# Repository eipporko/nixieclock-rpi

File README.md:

6 digit Nixie Clock
===================

## Motivation

* [Alex's Nixie Clock](https://www.raspberrypi.org/blog/alexs-nixie-clock/)

## Project structure

 * `hardware/eagle` - PCB design and schematics
 * `hardware/docs`  - various PDF datasheets for components used
 * `software`       - clock program

## BOM Summary
Main components

 * IN-8-2 Nixie tubes
 * MH74141 Nixie driver
 * 74HCT259 8-bit addressable latch
 * SN74LS77 4-bit D latch
 * ULN2803A Eight Darligton array
 * Raspberry Pi Zero, 1, 2 or 3 (Models B, B+)

The BCD decoder IC and Nixie tubes is hard to obtain, so far they're only
available on ebay and most of them are NOS(new old stock)

Check the schematics for the rest of the passives

## Theory of operation

### Architecture
Every digit of the display is composed by a Nixie tube (IN-8-2) driven by a
decimal decoder designed for directly drive this kind of gas-filled cold-cathode
indicators (MH74141) which input is supplied by a 4-bit D Latch (SN74LS77).

Each latch is multiplexed, with one 3-line to 8-line demux with latch (74HCT259),
in order to share the 4 bit bus with all the drivers.

In this way it's only needed 8 bits to control the clock's display.

```
** RPI GPIO HEADER SCHEMATIC **
                            .___.
                   +3V3---1-|O O|--2--+5V
           (SDA)  GPIO2---3-|O O|--4--+5V
          (SCL1)  GPIO3---5-|O O|--6--_
     (GPIO_GLCK)  GPIO4---7-|O O|--8-----GPIO14 (TXD0)
                       _--9-|O.O|-10-----GPIO15 (RXD0)
     (GPIO_GEN0) GPIO17--11-|O O|-12-----GPIO18 (GPIO_GEN1)
     (GPIO_GEN2) GPIO27--13-|O O|-14--_
     (GPIO_GEN3) GPIO22--15-|O O|-16-----GPIO23 (GPIO_GEN4)
                   +3V3--17-|O O|-18-----GPIO24 (GPIO_GEN5)
      (SPI_MOSI) GPIO10--19-|O.O|-20--_
      (SPI_MOSO) GPIO9 --21-|O O|-22-----GPIO25 (GPIO_GEN6)
      (SPI_SCLK) GPIO11--23-|O O|-24-----GPIO8  (SPI_C0_N)
                       _-25-|O O|-26-----GPIO7  (SPI_C1_N)
        (EEPROM) ID_SD---27-|O O|-28-----ID_SC Reserved for ID EEPROM
                 GPIO5---29-|O.O|-30--_
                 GPIO6---31-|O O|-32-----GPIO12
                 GPIO13--33-|O O|-34--_
                 GPIO19--35-|O O|-36-----GPIO16
                 GPIO26--37-|O O|-38-----GPIO20
                       _-39-|O O|-40-----GPIO21
                            '---'

** NIXIE DIGIT MESSAGE **

                 DATA            ADDRESS    STRBE
           ,--------------,    ,---------,  ,---,
           A    B    C    D    A    B    C    |
           |    |    |    |    |    |    |    |
        | $22  $18  $16  $15  $13  $12  $11  $7 |
        '---------------------------------------'

```

## Installation

### Configuring GPIO
```
sudo raspi-config
```
###

### Build clock

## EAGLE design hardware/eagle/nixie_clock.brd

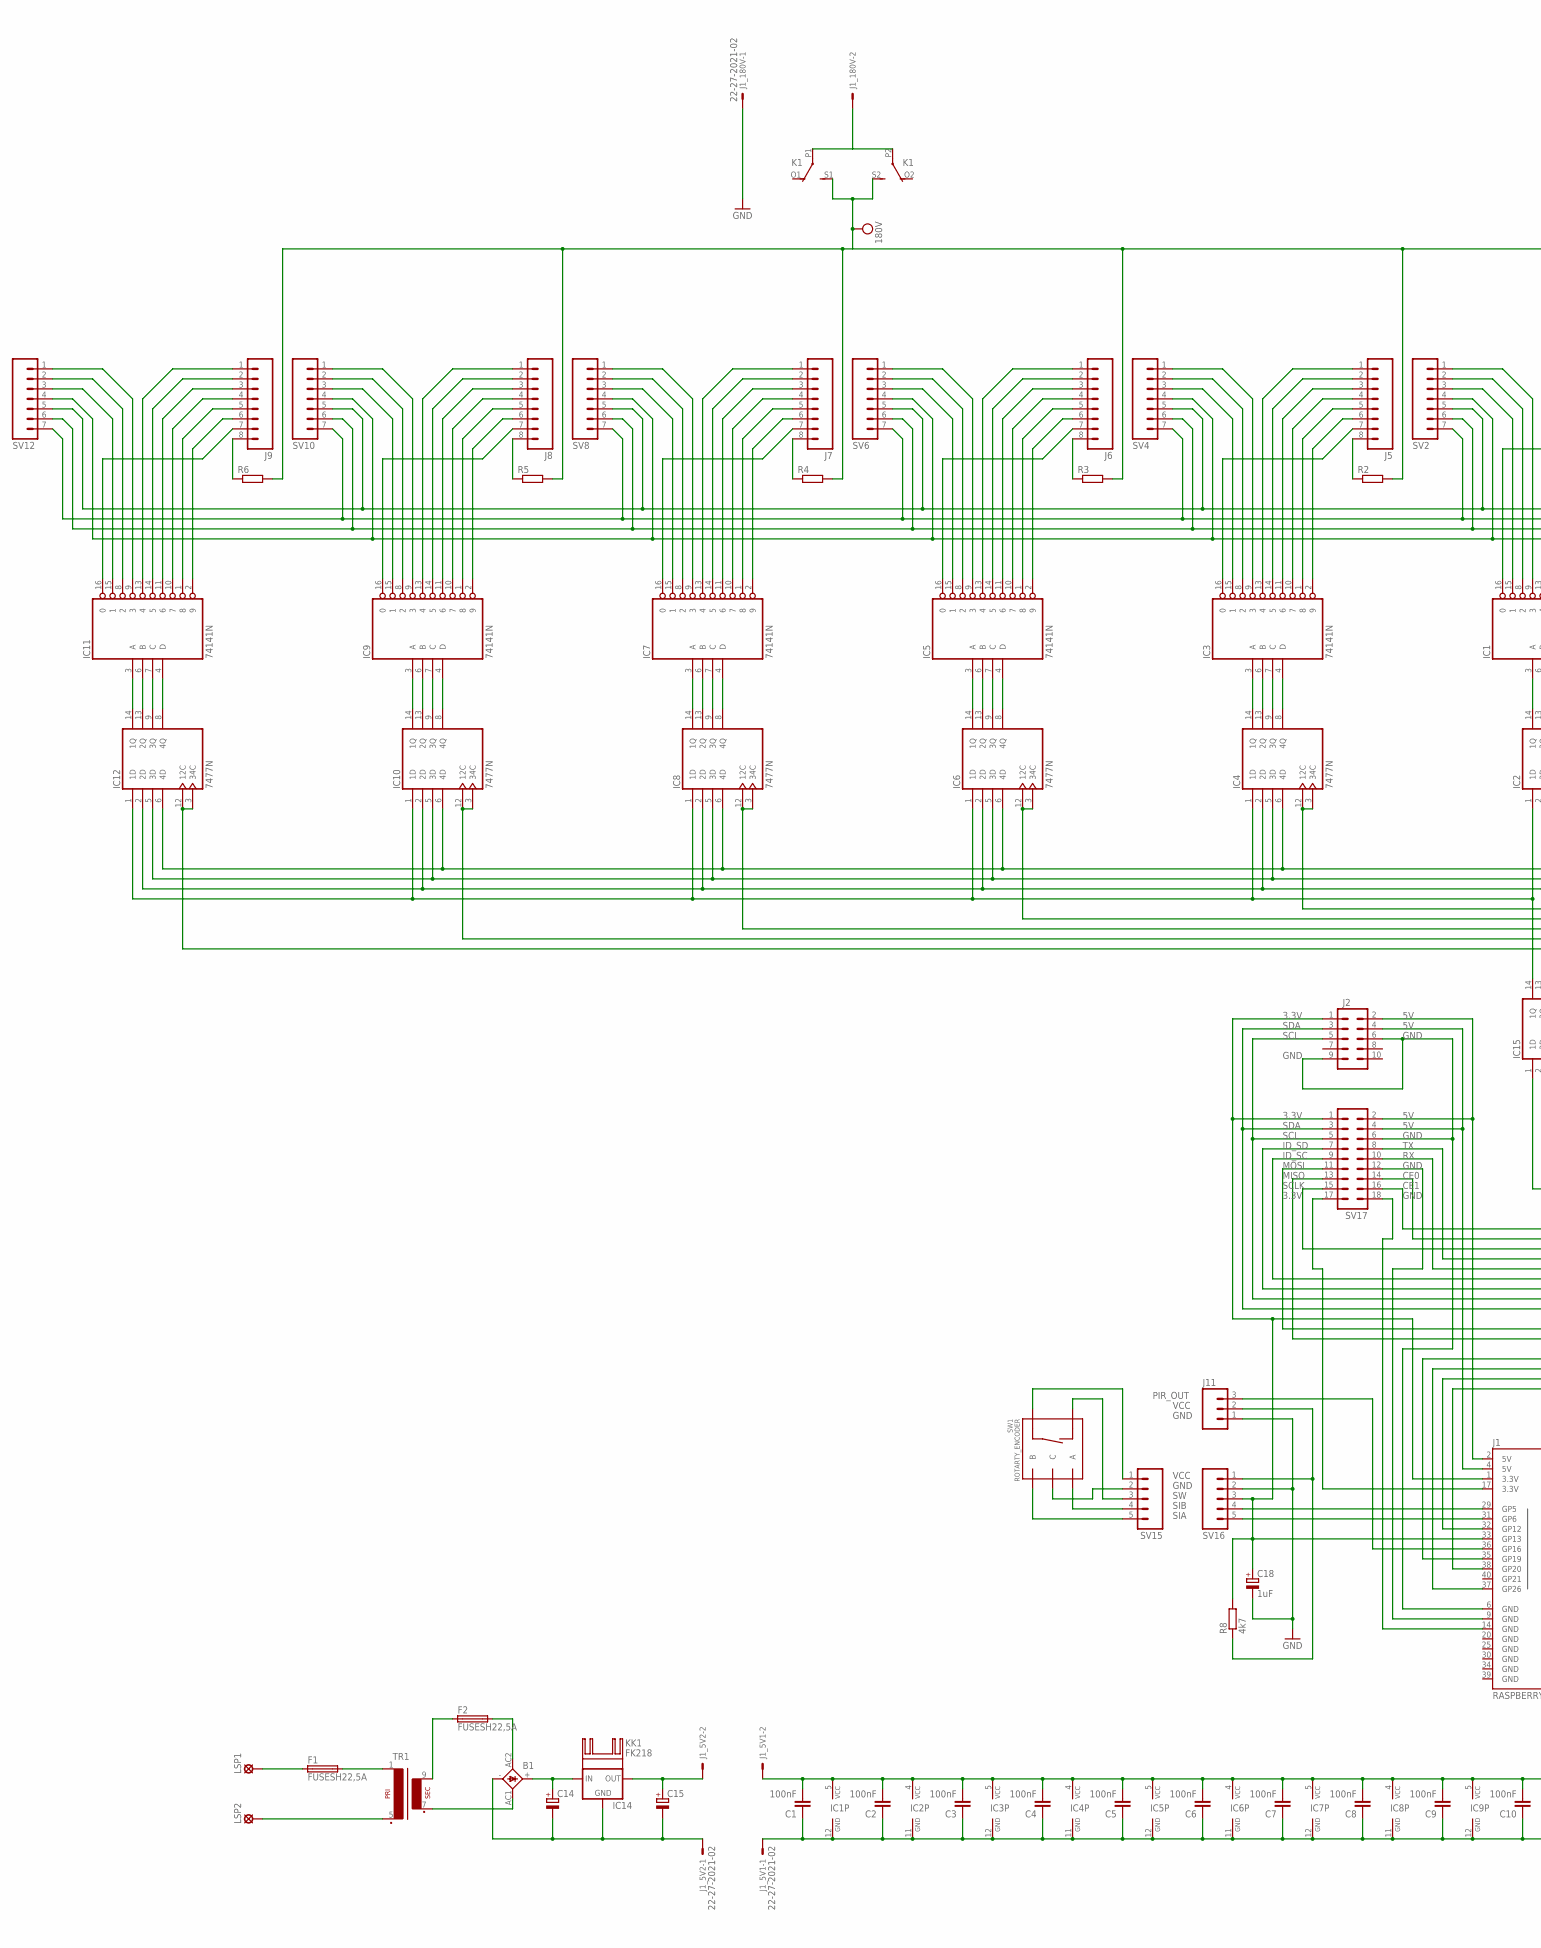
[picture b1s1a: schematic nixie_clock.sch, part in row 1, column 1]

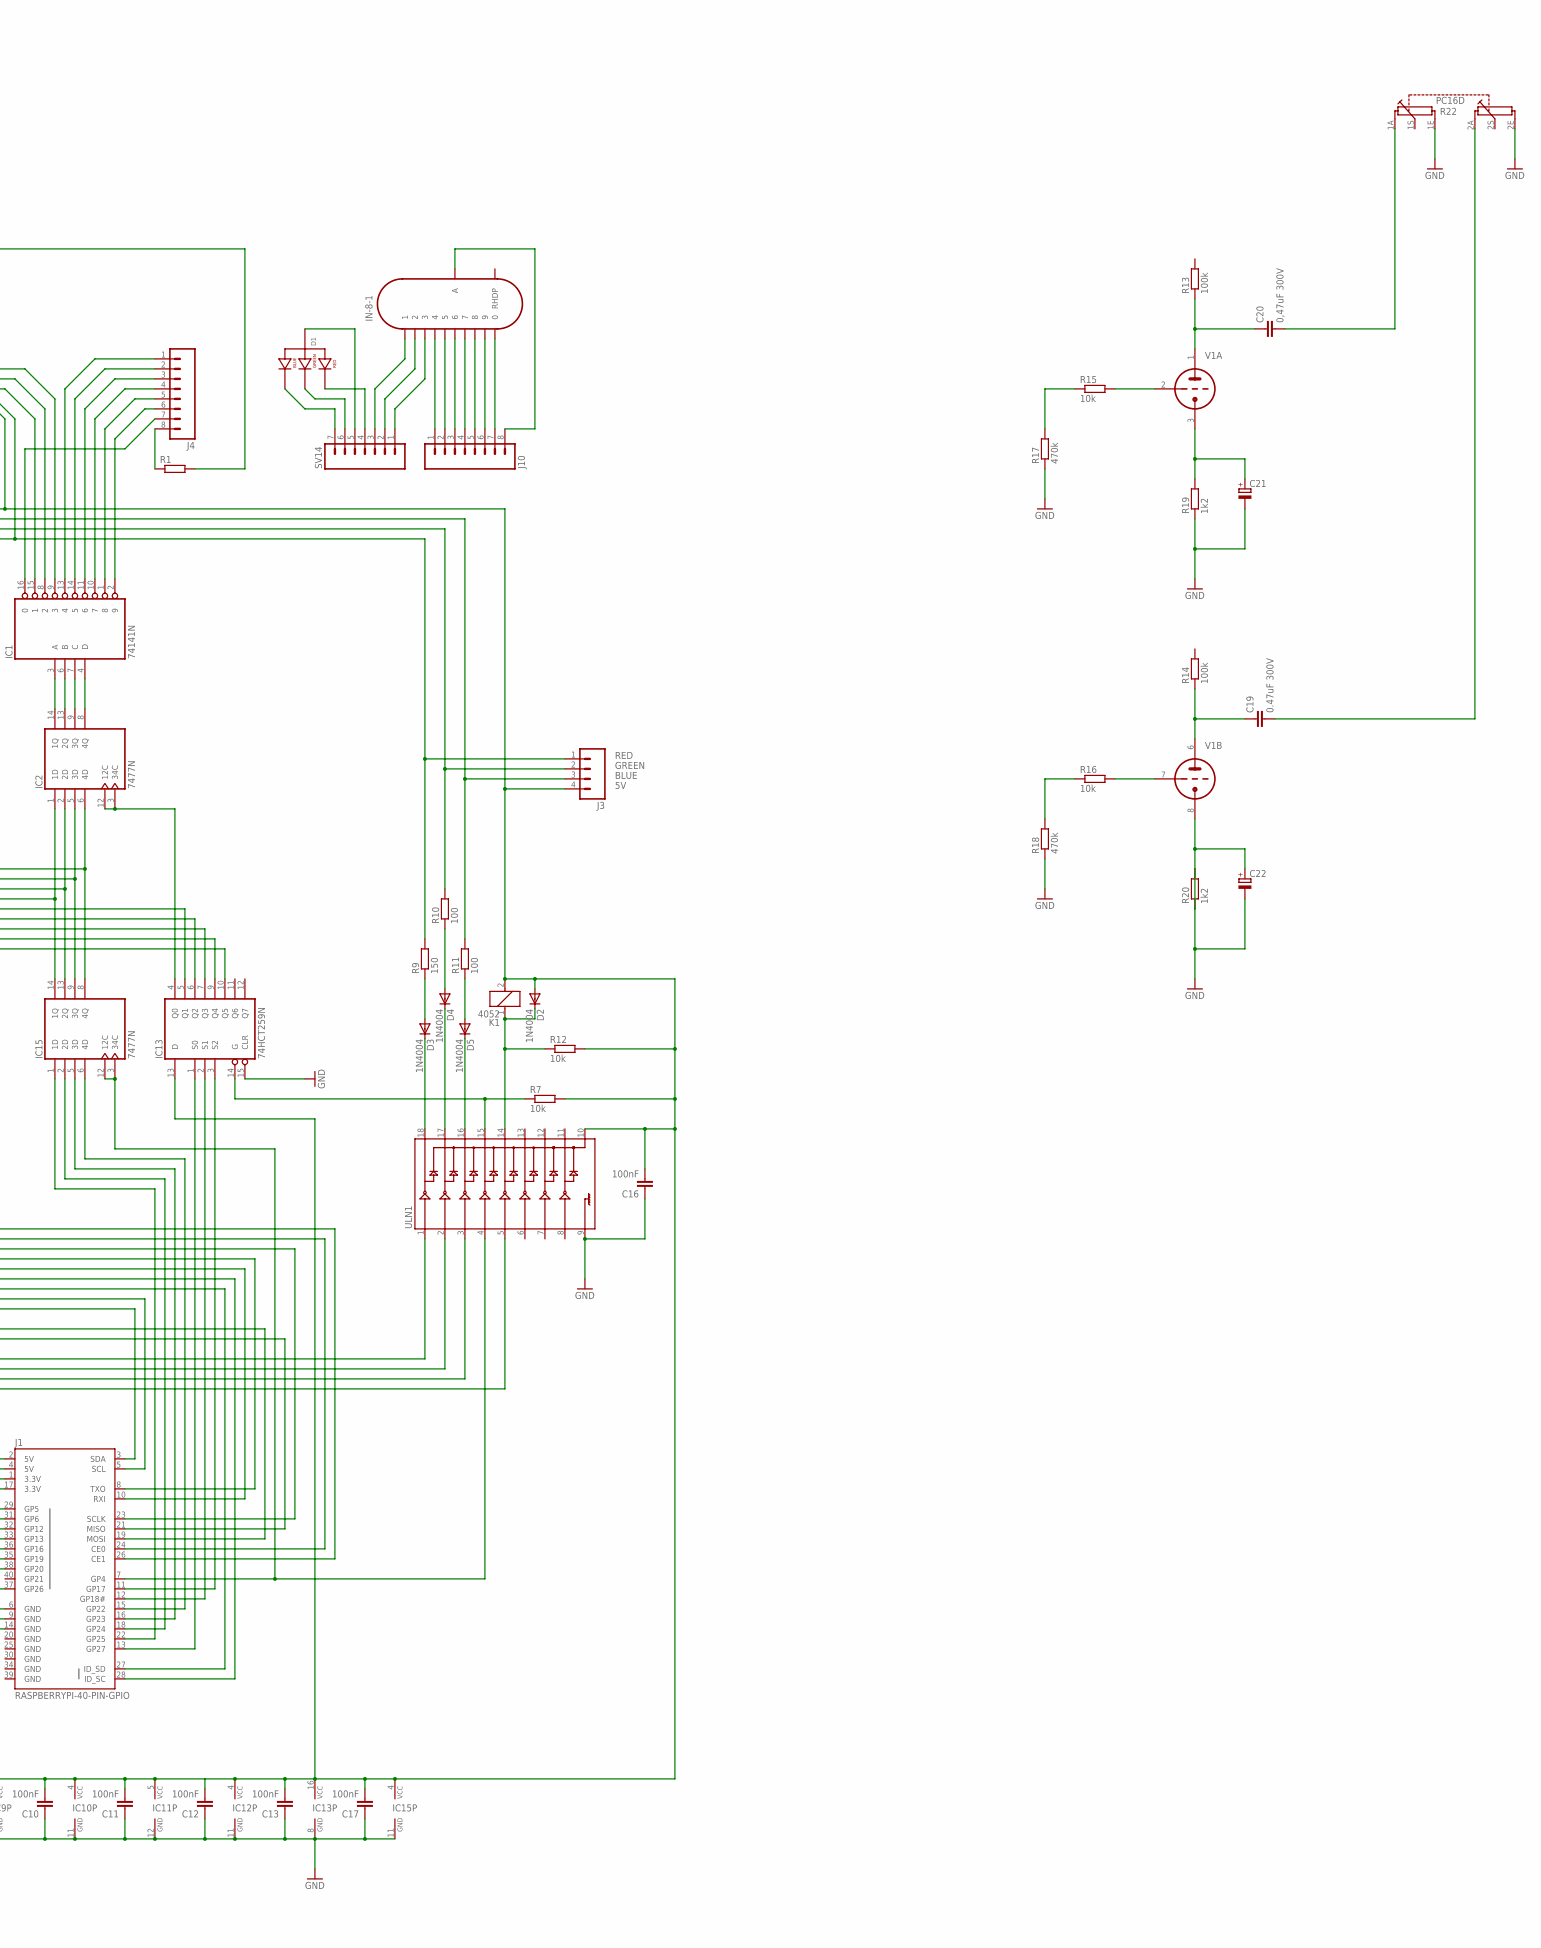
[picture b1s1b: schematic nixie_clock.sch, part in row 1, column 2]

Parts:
B1: FBP1,5
C1, C2, C3, C4, C5, C6, C7, C8, C9, C10, C11, C12, C13, C16, C17: 100nF; C025-024X044; MPN MCFYU6104Z6
C14: CPOL-EUE5-10.5; E5-10,5
C15: CPOL-EUE3.5-10; E3,5-10
C18: 1uF; E2,5-5
C19: 0.47uF 300V; C275-154X316
C20: 0,47uF 300V; C275-154X316
C21, C22: CPOL-EUE2.5-5; E2,5-5
D1: LED-RGB-CA-THRUCLEAR; LED-RGB-THRU
D2, D3, D4, D5: 1N4004; DO41-10
F1, F2: FUSESH22,5A; SH22,5A
IC1, IC3, IC5, IC7, IC9, IC11: 74141N; DIL16
IC2, IC4, IC6, IC8, IC10, IC12, IC15: 7477N; DIL14
IC13: 74HCT259N; DIL16
IC14: 78XXS
IN-8-1: IN-8-2
J1: RASPBERRYPI-40-PIN-GPIO; 2X20-SHROUDED
J1_5V1, J1_5V2, J1_180V: 22-27-2021-02; 6410-02
J2: M05X2PTH; AVR_ICSP
J3: M04; 04P
J4, J5, J6, J7, J8, J9, J10: M08; 1X08_ROUND
J11: M03; 03P
K1: 4052; F4052
KK1: FK218
LSP1, LSP2: LSP10
R1, R2, R3, R4, R5, R6: R-EU_0207/15; 0207/15; MPN MMA02040E5101BB100
R7, R12: 10k; 0204/7
R8: 4k7; 0204/7
R9: 150; 0204/7
R10, R11: 100; 0204/7
R13, R14: 100k; 0309/10
R15, R16: 10k; 0309/10
R17, R18: 470k; 0309/10
R19, R20: 1k2; 0309/10
R22: PC16D
SV2, SV4, SV6, SV8, SV10, SV12, SV14: M07; 1X07
SV15: M05PTH; 1X05
SV16: M05; 05P
SV17: MA09-2
SW1: ROTARTY_ENCODER; ROTARY_ENC_PLAIN
TR1: EI42-1
ULN1: ULN2803DIP; DIL18
V1: ECC82-P; NOVAL

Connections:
5V: C1.2, C2.2, C3.2, C4.2, C5.2, C6.2, C7.2, C8.2, C9.2, C10.2, C11.2, C12.2, C13.2, C16.2, C17.2, D2.A, IC1.5 (VCC), IC2.4 (VCC), IC3.5 (VCC), IC4.4 (VCC), IC5.5 (VCC), IC6.4 (VCC), IC7.5 (VCC), IC8.4 (VCC), IC9.5 (VCC), IC10.4 (VCC), IC11.5 (VCC), IC12.4 (VCC), IC13.13 (D), IC13.16 (VCC), IC15.4 (VCC), J1_5V1.2, J3.4, K1.2, R7.2, R12.2, SV2.5, SV4.5, SV6.5, SV8.5, SV10.5, SV12.5, ULN1.10
BLUE: J3.3, R11.2, SV2.7, SV4.7, SV6.7, SV8.7, SV10.7, SV12.7
GND: C1.1, C2.1, C3.1, C4.1, C5.1, C6.1, C7.1, C8.1, C9.1, C10.1, C11.1, C12.1, C13.1, C16.1, C17.1, C18.-, C21.-, IC1.12 (GND), IC2.11 (GND), IC3.12 (GND), IC4.11 (GND), IC5.12 (GND), IC6.11 (GND), IC7.12 (GND), IC8.11 (GND), IC9.12 (GND), IC10.11 (GND), IC11.12 (GND), IC12.11 (GND), IC13.8 (GND), IC13.15 (CLR), IC15.11 (GND), J1.20 (GND), J1.25 (GND), J1.30 (GND), J1.34 (GND), J1.39 (GND), J1_5V1.1, J1_180V.1, J11.1, R17.1, R18.1, R19.1, R22.1E, R22.2E, SV16.2, ULN1.9
GREEN: J3.2, R10.2, SV2.6, SV4.6, SV6.6, SV8.6, SV10.6, SV12.6
unnamed: IN-8-1.4, J10.1
unnamed: IC1.3 (A), IC2.14 (1Q)
unnamed: IC1.6 (B), IC2.13 (2Q)
unnamed: IC1.7 (C), IC2.9 (3Q)
unnamed: IC1.4 (D), IC2.8 (4Q)
unnamed: IN-8-1.5, J10.2
unnamed: IN-8-1.6, J10.3
unnamed: IN-8-1.7, J10.4
unnamed: IN-8-1.8, J10.5
unnamed: IN-8-1.9, J10.6
unnamed: IN-8-1.0, J10.7
unnamed: IN-8-1.3, SV14.1
unnamed: IN-8-1.2, SV14.2
unnamed: IN-8-1.1, SV14.3
unnamed: D1.1 (RED_CATHODE), SV14.4
unnamed: IC2.3 (34C), IC2.12 (12C), IC13.4 (Q0)
unnamed: IC2.6 (4D), IC4.6 (4D), IC6.6 (4D), IC8.6 (4D), IC10.6 (4D), IC12.6 (4D), IC15.8 (4Q)
unnamed: IC1.13 (4), J4.1
unnamed: IC1.14 (5), J4.2
unnamed: D1.4 (BLUE_CATHODE), SV14.7
unnamed: D1.2 (ANODE), SV14.5
unnamed: D1.3 (GREEN_CATHODE), SV14.6
unnamed: IC1.11 (6), J4.3
unnamed: IC1.10 (7), J4.4
unnamed: IC1.1 (8), J4.5
unnamed: IC1.2 (9), J4.6
unnamed: IC1.9 (3), SV2.1
unnamed: IC1.8 (2), SV2.2
unnamed: IC3.3 (A), IC4.14 (1Q)
unnamed: IC3.6 (B), IC4.13 (2Q)
unnamed: IC3.7 (C), IC4.9 (3Q)
unnamed: IC3.4 (D), IC4.8 (4Q)
unnamed: IC4.3 (34C), IC4.12 (12C), IC13.5 (Q1)
unnamed: IC1.15 (1), SV2.3
unnamed: IC1.16 (0), J4.7
unnamed: IC3.13 (4), J5.1
unnamed: IC3.14 (5), J5.2
unnamed: IC3.11 (6), J5.3
unnamed: IC3.10 (7), J5.4
unnamed: IC3.1 (8), J5.5
unnamed: IC3.2 (9), J5.6
unnamed: IC3.16 (0), J5.7
unnamed: IC3.9 (3), SV4.1
unnamed: IC5.3 (A), IC6.14 (1Q)
unnamed: IC5.6 (B), IC6.13 (2Q)
unnamed: IC5.7 (C), IC6.9 (3Q)
unnamed: IC5.4 (D), IC6.8 (4Q)
unnamed: IC6.3 (34C), IC6.12 (12C), IC13.6 (Q2)
unnamed: IC3.8 (2), SV4.2
unnamed: IC3.15 (1), SV4.3
unnamed: IC5.13 (4), J6.1
unnamed: IC5.14 (5), J6.2
unnamed: IC5.11 (6), J6.3
unnamed: IC5.10 (7), J6.4
unnamed: IC5.1 (8), J6.5
unnamed: IC5.2 (9), J6.6
unnamed: IC5.16 (0), J6.7
unnamed: IC5.9 (3), SV6.1
unnamed: IC7.3 (A), IC8.14 (1Q)
unnamed: IC7.6 (B), IC8.13 (2Q)
unnamed: IC7.7 (C), IC8.9 (3Q)
unnamed: IC7.4 (D), IC8.8 (4Q)
unnamed: IC8.3 (34C), IC8.12 (12C), IC13.7 (Q3)
unnamed: IC5.8 (2), SV6.2
unnamed: IC5.15 (1), SV6.3
unnamed: IC7.13 (4), J7.1
unnamed: IC7.14 (5), J7.2
unnamed: IC7.11 (6), J7.3
unnamed: IC7.10 (7), J7.4
unnamed: IC7.1 (8), J7.5
unnamed: IC7.2 (9), J7.6
unnamed: IC7.16 (0), J7.7
unnamed: IC7.9 (3), SV8.1
unnamed: IC9.3 (A), IC10.14 (1Q)
unnamed: IC9.6 (B), IC10.13 (2Q)
unnamed: IC9.7 (C), IC10.9 (3Q)
unnamed: IC9.4 (D), IC10.8 (4Q)
unnamed: IC10.3 (34C), IC10.12 (12C), IC13.9 (Q4)
unnamed: IC7.8 (2), SV8.2
unnamed: IC7.15 (1), SV8.3
unnamed: IC9.13 (4), J8.1
unnamed: IC9.14 (5), J8.2
unnamed: IC9.11 (6), J8.3
unnamed: IC9.10 (7), J8.4
unnamed: IC9.1 (8), J8.5
unnamed: IC9.2 (9), J8.6
unnamed: IC11.13 (4), J9.1
unnamed: IC11.14 (5), J9.2
unnamed: IC11.3 (A), IC12.14 (1Q)
unnamed: IC11.6 (B), IC12.13 (2Q)
unnamed: IC11.7 (C), IC12.9 (3Q)
unnamed: IC11.4 (D), IC12.8 (4Q)
unnamed: IC12.3 (34C), IC12.12 (12C), IC13.10 (Q5)
unnamed: IC2.5 (3D), IC4.5 (3D), IC6.5 (3D), IC8.5 (3D), IC10.5 (3D), IC12.5 (3D), IC15.9 (3Q)
unnamed: IC2.2 (2D), IC4.2 (2D), IC6.2 (2D), IC8.2 (2D), IC10.2 (2D), IC12.2 (2D), IC15.13 (2Q)
unnamed: IC2.1 (1D), IC4.1 (1D), IC6.1 (1D), IC8.1 (1D), IC10.1 (1D), IC12.1 (1D), IC15.14 (1Q)
unnamed: IC13.1 (S0), J1.13 (GP27)
unnamed: IC13.2 (S1), J1.12 (GP18#)
unnamed: IC13.3 (S2), J1.11 (GP17)
unnamed: IC9.16 (0), J8.7
unnamed: IC9.9 (3), SV10.1
unnamed: IC9.8 (2), SV10.2
unnamed: IC9.15 (1), SV10.3
unnamed: IN-8-1.A, J10.8
unnamed: IC11.11 (6), J9.3
unnamed: IC11.10 (7), J9.4
unnamed: IC11.1 (8), J9.5
unnamed: B1.+, C14.+, IC14.IN
unnamed: IC11.2 (9), J9.6
unnamed: IC11.16 (0), J9.7
unnamed: IC11.9 (3), SV12.1
unnamed: IC11.8 (2), SV12.2
unnamed: IC11.15 (1), SV12.3
unnamed: J8.8, R5.1
unnamed: J9.8, R6.1
unnamed: D4.C, ULN1.17
unnamed: F1.1, LSP1.MP
unnamed: F1.2, TR1.1
unnamed: LSP2.MP, TR1.5 (P2)
unnamed: F2.1, TR1.9 (S4)
unnamed: B1.AC2 (AC1), F2.2
unnamed: B1.AC1 (AC2), TR1.7 (S3)
unnamed: C15.+, IC14.OUT, J1_5V2.2
unnamed: J1.35 (GP19), ULN1.1
unnamed: B1.-, C14.-, C15.-, IC14.GND, J1_5V2.1
unnamed: J1_180V.2, K1.P1, K1.P2
unnamed: J1.37 (GP26), ULN1.2
unnamed: SV15.4, SW1.A
unnamed: J1.32 (GP12), ULN1.3
unnamed: C18.+, J1.1 (3.3V), J1.33 (GP13), J2.1, R8.2, SV16.3, SV17.1
unnamed: SV15.3, SW1.SW-
unnamed: SV15.1, SW1.SW+
unnamed: SV15.2, SW1.C
unnamed: SV15.5, SW1.B
unnamed: D3.C, ULN1.18
unnamed: D5.C, ULN1.16
unnamed: J1.31 (GP6), SV16.5
unnamed: J1.29 (GP5), SV16.4
unnamed: D3.A, R9.1
unnamed: IC13.14 (G), R7.1, ULN1.15
unnamed: IC15.1 (1D), J1.22 (GP25)
unnamed: IC15.2 (2D), J1.18 (GP24)
unnamed: IC15.5 (3D), J1.16 (GP23)
unnamed: IC15.6 (4D), J1.15 (GP22)
unnamed: IC15.3 (34C), IC15.12 (12C), J1.7 (GP4), ULN1.4
unnamed: D4.A, R10.1
unnamed: D5.A, R11.1
unnamed: J1.38 (GP20), ULN1.5
unnamed: J7.8, R4.1
unnamed: D2.C, K1.1, R12.1, ULN1.14
unnamed: J1.17 (3.3V), SV17.17
unnamed: J1.4 (5V), J2.4, SV17.4
unnamed: J1.3 (SDA), J2.3, SV17.3
unnamed: J1.5 (SCL), J2.5, SV17.5
unnamed: J1.6 (GND), J2.6, J2.9, SV17.6
unnamed: J1.27 (ID_SD), SV17.7
unnamed: J1.28 (ID_SC), SV17.9
unnamed: J1.8 (TXO), SV17.8
unnamed: J1.10 (RXI), SV17.10
unnamed: J1.19 (MOSI), SV17.11
unnamed: J1.21 (MISO), SV17.13
unnamed: J1.23 (SCLK), SV17.15
unnamed: J4.8, R1.1
unnamed: J1.9 (GND), SV17.12
unnamed: J1.24 (CE0), SV17.14
unnamed: J1.26 (CE1), SV17.16
unnamed: J1.14 (GND), SV17.18
unnamed: J6.8, R3.1
unnamed: R1.2, R2.2, R3.2, R4.2, R5.2, R6.2
unnamed: J5.8, R2.1
unnamed: J1.2 (5V), J2.2, SV17.2
unnamed: J1.36 (GP16), J11.3
unnamed: R15.1, R17.2
unnamed: R16.1, R18.2
unnamed: R15.2, V1.2 (TG)
unnamed: C20.1, R13.1, V1.1 (TA)
unnamed: C19.1, R14.1, V1.6 (TA)
unnamed: R16.2, V1.7 (TG)
unnamed: C22.+, C22.-, R20.1, R20.2, V1.8 (TK)
unnamed: C21.+, R19.2, V1.3 (TK)
unnamed: J11.2, R8.1, SV16.1
unnamed: C20.2, R22.1A
unnamed: C19.2, R22.2A
RED: J3.1, R9.2, SV2.4, SV4.4, SV6.4, SV8.4, SV10.4, SV12.4
VCC: K1.S1 (S), K1.S2 (S)

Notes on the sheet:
SIA
SIB
GND
VCC
3.3V
SDA
SCL
ID_SD
ID_SC
MOSI
MISO
SCLK
CE0
CE1
PIR_OUT

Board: 2 copper layers, 99 parts (4 on the bottom side), 189 nets, no tracks yet.

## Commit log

2016-06-10 First test with wiringPi
2016-06-10 Added build script
2016-06-11 Added time examples
2016-06-11 Added clock program (scheleton)
2016-06-12 Multiplexed output
2016-06-12 Added nixie tubes testing
2016-06-13 First board
2016-06-14 Updated eagle project
2016-06-15 External nixie tubes design
2016-06-18 Added power supply on eagle project
2016-06-19 FreeCad nixie model
2016-06-19 Updated project
2016-06-19 Updated eagle library
2016-06-23 Added relay
2016-06-26 Added rotary encoder example
2016-06-26 Update project
2016-06-30 RGB led fading with rotary encoder
2016-07-03 Working on Sunday
2016-07-04 Added uln documentation
2016-07-06 Added a Toroidal transformer
2016-07-13 Added new model on freecad model and updated pcb board
2016-07-17 Updated project: new documentation & more ...
2016-07-25 Fixed some issues related with the multiplexed data
2016-07-26 Updated clock.c and removed rencoder test
2016-08-11 Fixed bug related to multiplexed data
2016-10-04 Updated eagle.epf file
2016-10-10 Added conds in piThreads
2016-10-12 Fixed CPU consumption with rotary encoder
2016-10-13 Fixed problem related with the elapsed time method
2016-10-16 CPU consumption improvement
2016-10-16 Added countdown timer in relay
2017-05-15 freecad model updated
2017-08-07 Fixed problem related with the pcb

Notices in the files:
parts and their libraries:
SparkFun-Electromechanical: Licensing: Creative Commons ShareAlike 4.0 International - https://creativecommons.org/licenses/by-sa/4.0
